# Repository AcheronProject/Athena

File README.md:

# Acheron Athena

## Introduction

Athena is a tenkeyless (TKL) keyboard Printed Circuit Board (PCB) which main feature is the multi-layout support. Athena supports:

- 87 (F12) or 88 (F13) TKL function rows;
- ANSI and ISO layouts
- 7U and 6.25U spacebar bottom row layouts
- Split backspace
- Split right shift

Below is a [Keyboard Layout Editor](http://keyboard-layout-editor.com/) image of the layouts Athena supports.

In [this link](https://raw.githubusercontent.com/Gondolindrim/file_hosting/main/athena/athena_KLE.json) there is a KLE JSON file for the layout.

Both Apollo and Athena line of PCBs were designed to be "universal" TKL PCBs, that is, designed to fit a wide variety of custom mechanical keyboards. The compatibility list is being built as more people check and test. See the **Keyboard compatibility** section of this README for the available list.

## Technical information

- Layout size: tenkeykess (TKL)
- Compatible switches: MX-like only, solderable
- Lighting: single colors per-key through-hole LEDs, RGB underglow
- Microcontroller: STM32 family (see [the Joker topologyt documentaton](https://acheronproject.com/multimcu_article/multimcu_article/))
- Connector: detachable USB Type C on the top side and JST connector for daughterboard support
- Firmware compatibility: QMK (with VIA support)
- Protection hardware:
  * USB data lines and power rail ESD suppressing
  * USB power overvoltage protection
  * Enclosure grounding pad
  * Overcurrent protection
  * LDO crowbar diode
  * EMI suppression (shielding ferrite bead)
- Current release: release Alpha-RC1 (pre-release candidate)
- Designer: Gondolindrim
- License: Acheron Open-Source Hardware License version 1.3

## Keyboard compatibility

## Known compatibilities

- **Geonworks F1-8X and F1-6X:** confirmed by Geon, who tested the PCB 3D files against the case 3D files. Live hardware testing into a machined case is pending.

### Known incompatibilities

- **ai03 KBD8X MKII**: ai03 open-sourced the PCB files for his KBD8X. Alghtough Apollo's edges do fit inside the original PCB's, its connector is more protruded then the original PCB's.

- **PrismA18**: different layouts on the function row.

## Acknowledgements

- Geon, who kindly spent time helping design this PCB to fit his keyboards.

## Copyright notice

This project is released under the Acheron Open-Hardware License V1.3. For the license, please refer to the LICENCE.md file.

The "athena with shield" logo was licensed through Adobe Stock in [this link](https://stock.adobe.com/hu/images/greek-goddess-athena-illustration/157297137); the source file in Adobe Illustrator format, with a converted ``.svg`` format  can be found in ``./resources/athena_logo``. The license was obtained in may 06, 2021 and allows the AcheronProject to redistribute the logo as open-source and allows anyone to sell the PCBs commercially, but it does not allow for reproduction, meaning that if you want to use the logo for your designs or products you will have to buy a license yourself.

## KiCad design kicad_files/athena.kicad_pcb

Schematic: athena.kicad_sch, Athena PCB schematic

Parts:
C1, C2, C7: 100n; C_0805_2012Metric
C3, C4, C5, C13: 100n; C_0402_1005Metric
C6, C14: 4.7u; C_0402_1005Metric
C8: 1u; C_0402_1005Metric
C9: 10n; C_0402_1005Metric
C10, C11: 1u; CP_EIA-3216-10_Kemet-I_Pad1.58x1.35mm_HandSolder
C12: 10u; C_0805_2012Metric
D1, D2, D3, D4, D5, D6, D7, D8, D9, D10, D11, D12, D13, D14, D15, D16, D17, D18, D19, D20, D21, D22, D23, D24, D25, D26, D27, D28, D29, D30, D31, D32, D33, D34, D35, D36, D37, D38, D39, D40, D41, D42, D43, D44, D45, D46, D47, D48, D49, D50, D51, D52, D53, D54, D55, D56, D57, D58, D59, D60, D61, D62, D63, D64, D65, D66, D67, D68, D69, D70, D71, D72, D73, D74, D75, D76, D77, D78, D79, D80, D81, D82, D83, D84, D85, D86, D87, D88, D89, D90, D91, D92, D94: 1N4148W; D_SOD-123
D93: RB060M-60TR; D_SOD-123; Manufacturer Part Number RB060M-60TR; LCSC Part Number C114257
F1: mSMD110-16V; Fuse_1812_4532Metric; Manufacturer Part Number mSMD110-16V; LCSC Part Number C69691
FB1: CBW201209U121T; L_0805_2012Metric; Manufacturer Part Number CBW201209U121T; LCSC Part Number C139186
H1: MountingHole; MountingHole_2.5x4.0mm
J1, J3: SM04B-SRSS-TB(LF)(SN); SM04B-SRSS-TB(LF)(SN)_mounting-reliefs; Manufacturer Part Number SM04B-SRSS-TB(LF)(SN); LCSC Part Number C160404
J2: TYPE-C-31-M12; TYPE-C-31-M-12; Manufacturer Part Number TYPE-C-31-M-12; LCSC Part Number C165948
J4: ARM JTAG; Conn_ARM_JTAG_SWD_6
J5: EXTRA PINS; PinHeader_1x5_P2.54mm_Vertical
Q1: DTC123JKAT146; SOT-23; Manufacturer Part Number DTC123JKAT146; LCSC Part Number C111724
R1: 10k; R_0805_2012Metric
R2, R3: 5.1k; R_0805_2012Metric
R4, R5: 1.5k; R_0402_1005Metric
R6: 100R; R_0805_2012Metric
R7, R8: 100k; R_0805_2012Metric
R9: 330k; R_0805_2012Metric
R10: 1M; R_0805_2012Metric
SW1, SW2, SW3, SW4, SW5, SW6, SW7, SW8, SW9, SW10, SW11, SW12, SW13, SW14, SW15, SW16, SW17, SW18, SW19, SW20, SW21, SW22, SW23, SW24, SW25, SW26, SW27, SW28, SW29, SW30, SW31, SW32, SW33, SW34, SW35, SW36, SW37, SW38, SW40, SW41, SW43, SW44, SW45, SW46, SW47, SW48, SW49, SW50, SW51, SW52, SW53, SW54, SW56, SW57, SW58, SW60, SW61, SW62, SW63, SW64, SW65, SW66, SW67, SW68, SW69, SW70, SW71, SW73, SW74, SW75, SW79, SW80, SW81, SW82, SW83, SW84, SW85, SW86, SW87, SW88, SW89, SW91, SW92, SW103, SW104, SW105, SW107, SW111: MX Switch; MX100
SW39: MX Switch; MX200
SW42, SW55, SW106, SW108, SW110, SW112: MX Switch; MX150
SW59, SW93: MX Switch; MX175
SW72: MX Switch; MX225R
SW76, SW94, SW95, SW96, SW97, SW99, SW100, SW101, SW102: MX Switch; MX125
SW77: MX Switch; MX_ISOEnter_Horizontal
SW78: MX Switch; MX225
SW90: MX Switch; MX275
SW98: MX Switch; MX625R
SW109: MX Switch; MX700R
SW113: K2-1187SQ-A4SW-06; Manufacturer Part Number K2-1187SQ-A4SW-06; LCSC Part Number C92584
U1: TXS0101DBVR; SOT-23-6; Manufacturer Part Number TXS0101DBVR; LCSC Part Number C132604
U2: USBLC6-2SC6; SOT-23-6; Manufacturer Part Number USBLC6-2SC6; LCSC Part Number C7519
U3: STM32F072CBT6; LQFP-48_7x7mm_P0.5mm; Manufacturer Part Number STM32F072CBT6; LCSC Part Number C81720
U4: MCP1700T-3302E/TT; SOT-23; Manufacturer Part Number MCP1700T-3302E/TT; LCSC Part Number C39051

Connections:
3V3: C1.2, C3.1, C4.1, C5.2, C6.2, C8.1, C9.1, C11.1, C13.2, C14.2, D93.2 (A), J4.1, J5.4, R1.1, R4.1, R5.1, R8.1, SW113.1 (A), U1.1 (VCCA), U3.1 (VBAT), U3.9 (VDDA), U3.24 (VDD), U3.36 (VDDIO2), U3.48 (VDD), U4.2 (VO)
5V: C2.1, C10.1, D93.1 (K), F1.2, J1.1, J3.1, R7.1, U1.6 (VCCB), U4.3 (VI)
BOOT0: C12.2, J4.6, R9.2, R10.2, U3.44 (BOOT0)
C0: SW1.2, SW26.2, SW42.2, SW59.2, SW76.1, SW78.2, SW94.2, SW95.2, SW106.2, U3.16 (PA6/ADC_IN6/TIM3_CH1/TIM16_CH1)
C1: SW2.1, SW27.1, SW43.1, SW60.1, SW79.1, SW96.1, SW107.1, U3.15 (PA5/ADC_IN5/DAC_OUT2)
C2: SW3.1, SW18.2, SW28.1, SW44.1, SW61.1, SW80.1, SW97.1, SW108.1, U3.14 (PA4/TIM14_CH1/ADC_IN4)
C3: SW4.1, SW19.2, SW29.1, SW45.1, SW62.1, SW81.1, U3.13 (PA3/TIM15_CH2/ADC_IN3)
C4: SW5.1, SW20.2, SW30.1, SW46.1, SW63.1, SW82.1, U3.12 (PA2/ADC_IN2)
C5: SW6.1, SW21.2, SW31.1, SW47.1, SW64.1, SW83.1, U3.40 (SPI1_MISO/I2S1_MCK/TIM3_CH1/PB4)
C6: SW7.1, SW32.1, SW48.1, SW65.1, SW84.1, SW98.2, SW109.2, U3.39 (SPI1_SCK/I2S1_CK/TIM2_CH2/PB3)
C7: SW8.1, SW33.1, SW49.1, SW66.1, SW85.1, U3.38 (PA15)
C8: SW9.1, SW34.1, SW50.1, SW67.1, SW86.1, U3.30 (TIM1_CH2/PA9)
C9: SW10.1, SW22.2, SW35.1, SW51.1, SW68.1, SW87.1, SW99.2, SW110.2, U3.29 (TIM1_CH1/PA8)
C10: SW11.2, SW23.1, SW36.1, SW52.1, SW69.1, SW88.1, SW100.2, U3.27 (SPI2_MISO/I2S2_MCK/I2C2_SDA/TIM15_CH1/P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)
C11: SW12.2, SW24.1, SW37.1, SW53.1, SW70.1, SW89.1, SW101.2, U3.25 (PB12)
C12: SW13.2, SW25.1, SW38.1, SW54.1, SW71.1, SW90.1, SW93.1, U3.21 (PB10/SPI2_SCK/I2C2_SCL/TIM2_CH3)
C13: SW14.1, SW39.1, SW41.1, SW55.1, SW72.1, SW77.1, SW91.1, SW102.1, SW112.1, U3.31 (TIM1_CH3/PA10)
C14: SW15.2, SW40.1, SW56.2, SW73.2, SW103.1, U3.10 (PA0/ADC_IN0)
C15: SW16.1, SW57.1, SW74.1, SW92.1, SW104.2, U3.5 (PF0/OSC_IN)
C16: SW17.1, SW58.1, SW75.1, SW105.1, U3.6 (PF1/OSC_OUT)
D+: J3.3, U2.1 (I/O1), U3.33 (USB_DP/PA12)
D-: J3.2, U2.3 (I/O2), U3.32 (USB_DM/TIM1_CH4/PA11)
DBUS+: J2.A6 (D+), J2.B6 (D+), U2.6 (I/O1)
DBUS-: J2.A7 (D-), J2.B7 (D-), U2.4 (I/O2)
GND: C1.1, C2.2, C3.2, C4.2, C5.1, C6.1, C7.2, C8.2, C9.2, C10.2, C11.2, C12.1, C13.1, C14.1, FB1.1, J1.2, J1.4, J1.MP (MountPin), J2.A1 (GND), J2.B1 (GND), J3.4, J3.MP (MountPin), J4.5, J5.5, Q1.2 (E), R2.1, R3.1, R7.2, R8.2, R10.1, U1.2 (GND), U2.2 (GND), U3.8 (VSSA), U3.23 (VSS), U3.35 (VSS), U3.47 (VSS), U4.1 (GND)
GNDPWR: FB1.2, H1.1, J2.S (SHIELD)
INTB: U3.45 (I2C1_SCL/TIM16_CH1/PB8)
NRST: C7.1, J4.3, R6.2, U3.7 (NRST)
unnamed: D1.2 (A), SW1.1
unnamed: D2.2 (A), SW2.2
unnamed: D3.2 (A), SW3.2, SW18.1
unnamed: D4.2 (A), SW4.2, SW19.1
unnamed: D5.2 (A), SW5.2, SW20.1
unnamed: D6.2 (A), SW6.2, SW21.1
unnamed: D7.2 (A), SW7.2
unnamed: D8.2 (A), SW8.2
unnamed: D9.2 (A), SW9.2
unnamed: D10.2 (A), SW10.2, SW22.1
unnamed: D11.2 (A), SW11.1, SW23.2
unnamed: D12.2 (A), SW12.1, SW24.2
unnamed: D13.2 (A), SW13.1, SW25.2
unnamed: D14.2 (A), SW14.2
unnamed: D15.2 (A), SW15.1
unnamed: D16.2 (A), SW16.2
unnamed: D17.2 (A), SW17.2
unnamed: D18.2 (A), SW26.1
unnamed: D19.2 (A), SW27.2
unnamed: D20.2 (A), SW28.2
unnamed: D21.2 (A), SW29.2
unnamed: D22.2 (A), SW30.2
unnamed: D23.2 (A), SW31.2
unnamed: D24.2 (A), SW32.2
unnamed: D25.2 (A), SW33.2
unnamed: D26.2 (A), SW34.2
unnamed: D27.2 (A), SW35.2
unnamed: D28.2 (A), SW36.2
unnamed: D29.2 (A), SW37.2
unnamed: D30.2 (A), SW38.2
unnamed: D31.2 (A), SW39.2, SW41.2
unnamed: D32.2 (A), SW40.2
unnamed: D33.2 (A), SW42.1
unnamed: D34.2 (A), SW43.2
unnamed: D35.2 (A), SW44.2
unnamed: D36.2 (A), SW45.2
unnamed: D37.2 (A), SW46.2
unnamed: D38.2 (A), SW47.2
unnamed: D39.2 (A), SW48.2
unnamed: D40.2 (A), SW49.2
unnamed: D41.2 (A), SW50.2
unnamed: D42.2 (A), SW51.2
unnamed: D43.2 (A), SW52.2
unnamed: D44.2 (A), SW53.2
unnamed: D45.2 (A), SW54.2
unnamed: D46.2 (A), SW55.2
unnamed: D47.2 (A), SW56.1
unnamed: D48.2 (A), SW57.2
unnamed: D49.2 (A), SW58.2
unnamed: D50.2 (A), SW59.1, SW76.2
unnamed: D51.2 (A), SW60.2
unnamed: D52.2 (A), SW61.2
unnamed: D53.2 (A), SW62.2
unnamed: D54.2 (A), SW63.2
unnamed: D55.2 (A), SW64.2
unnamed: D56.2 (A), SW65.2
unnamed: D57.2 (A), SW66.2
unnamed: D58.2 (A), SW67.2
unnamed: D59.2 (A), SW68.2
unnamed: D60.2 (A), SW69.2
unnamed: D61.2 (A), SW70.2
unnamed: D62.2 (A), SW71.2
unnamed: D63.2 (A), SW72.2, SW77.2
unnamed: D64.2 (A), SW73.1
unnamed: D65.2 (A), SW74.2
unnamed: D66.2 (A), SW75.2
unnamed: D67.2 (A), SW78.1, SW94.1
unnamed: D68.2 (A), SW79.2
unnamed: D69.2 (A), SW80.2
unnamed: D70.2 (A), SW81.2
unnamed: D71.2 (A), SW82.2
unnamed: D72.2 (A), SW83.2
unnamed: D73.2 (A), SW84.2
unnamed: D74.2 (A), SW85.2
unnamed: D75.2 (A), SW86.2
unnamed: D76.2 (A), SW87.2
unnamed: D77.2 (A), SW88.2
unnamed: D78.2 (A), SW89.2
unnamed: D79.2 (A), SW90.2, SW93.2
unnamed: D80.2 (A), SW91.2
unnamed: D81.2 (A), SW92.2
unnamed: D82.2 (A), SW95.1, SW106.1
unnamed: D83.2 (A), SW96.2, SW107.2
unnamed: D84.2 (A), SW97.2, SW108.2
unnamed: D85.2 (A), SW98.1, SW109.1
unnamed: D86.2 (A), SW99.1, SW110.1
unnamed: D87.2 (A), SW100.1
unnamed: D88.2 (A), SW101.1
unnamed: D89.2 (A), SW102.2, SW112.2
unnamed: D90.2 (A), SW103.2
unnamed: D91.2 (A), SW104.1
unnamed: D92.2 (A), SW105.2
unnamed: D94.1 (K), R9.1
unnamed: D94.2 (A), Q1.1 (B), SW113.2 (B)
unnamed: J2.A5 (CC1), R2.2
unnamed: J2.B5 (CC2), R3.2
unnamed: Q1.3 (C), R6.1
unnamed: R1.2, U1.5 (OE)
PC13: J5.1, U3.2 (PC13)
PC14: J5.2, U3.3 (PC14/OSC32_IN)
PC15: J5.3, U3.4 (PC15/OSC32_OUT)
R0: D1.1 (K), D2.1 (K), D3.1 (K), D4.1 (K), D5.1 (K), D6.1 (K), D7.1 (K), D8.1 (K), D9.1 (K), D10.1 (K), D11.1 (K), D12.1 (K), D13.1 (K), D14.1 (K), D15.1 (K), D16.1 (K), D17.1 (K), U3.18 (PB0/TIM3_CH3/ADC_IN8)
R1: D18.1 (K), D19.1 (K), D20.1 (K), D21.1 (K), D22.1 (K), D23.1 (K), D24.1 (K), D25.1 (K), D26.1 (K), D27.1 (K), D28.1 (K), D29.1 (K), D30.1 (K), D31.1 (K), D32.1 (K), U3.19 (PB1/TIM3_CH4/TIM14_CH1/ADC_IN9)
R2: D33.1 (K), D34.1 (K), D35.1 (K), D36.1 (K), D37.1 (K), D38.1 (K), D39.1 (K), D40.1 (K), D41.1 (K), D42.1 (K), D43.1 (K), D44.1 (K), D45.1 (K), D46.1 (K), D47.1 (K), D48.1 (K), D49.1 (K), U3.20 (PB2)
R3: D50.1 (K), D51.1 (K), D52.1 (K), D53.1 (K), D54.1 (K), D55.1 (K), D56.1 (K), D57.1 (K), D58.1 (K), D59.1 (K), D60.1 (K), D61.1 (K), D62.1 (K), D63.1 (K), D64.1 (K), D65.1 (K), D66.1 (K), U3.22 (PB11/TIM2_CH4/I2C2_SDA)
R4: D67.1 (K), D68.1 (K), D69.1 (K), D70.1 (K), D71.1 (K), D72.1 (K), D73.1 (K), D74.1 (K), D75.1 (K), D76.1 (K), D77.1 (K), D78.1 (K), D79.1 (K), D80.1 (K), D81.1 (K), U3.11 (PA1/ADC_IN1)
R5: D82.1 (K), D83.1 (K), D84.1 (K), D85.1 (K), D86.1 (K), D87.1 (K), D88.1 (K), D89.1 (K), D90.1 (K), D91.1 (K), D92.1 (K), U3.17 (PA7/TIM3_CH2/TIM14_CH1/ADC_IN7)
RGB_3V3: U1.3 (A), U3.28 (SPI2_MOSI/I2S2_SD/PB15)
RGB_5V: J1.3, U1.4 (B)
SCL: R5.2, U3.42 (I2C1_SCL/PB6)
SDA: R4.2, U3.43 (2C1_SDA/PB7)
SDB: U3.41 (SPI1_MOSI/I2S1_SD/TIM3_CH2/PB5)
SWCLK: J4.4, U3.37 (SWCLK/PA14)
SWDIO: J4.2, U3.34 (SWDIO/PA13)
VBUS: F1.1, J2.A4 (VBUS), J2.B4 (VBUS), U2.5 (VBUS)

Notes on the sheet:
USB Connector
USB ESD
MCU
SWITCH MATRIX
3V3
RGB STRIP
HARD RESET

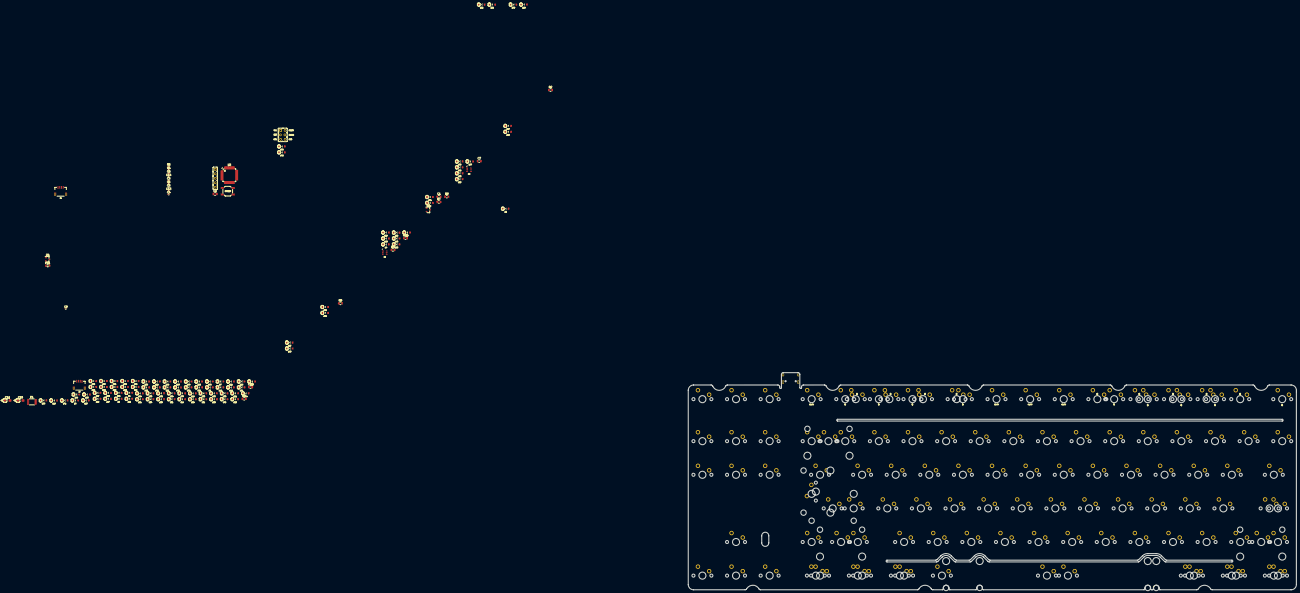
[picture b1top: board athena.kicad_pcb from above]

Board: 2 copper layers, 344.7 x 123.1 mm, 242 parts (1 on the bottom side), 140 nets, no tracks yet.

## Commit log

2021-05-07 Further developments
    - Define PCB edges
    - Place switches and layouts
    - Place USBC connector
2021-05-07 Added Athena logo
2021-05-08 Route first row and most USB, add LEDs
2021-09-25 Acheron Setup port, joker topology
    - Tolerances and constraints were updated to Acheron Setup's defaults
    - New MCU "joker" topology
2021-09-25 Update submodules
2021-09-26 Routing work
2021-09-27 Routing work, USB DB sketch
2021-09-28 More routing, DRC and post-routing pending
2021-10-01 Added logos, some DRC
2021-10-02 Add warning signs, DRC ran, errors fixed
2021-10-05 MCU circuit topology, QOL updates
    - Both RCC resistors for USB are now in the bottom layer
    - DRC ran again, no errors found
    - Changed MCU template to the joker revision 2, meaning removal of some bypass capacitors, adittion of a tantallum 10uF capacitor for VDD and change VCAP pin capacitor to 4.7uF from 2.2uF
2021-10-09 Implement B87X2 outline
2021-10-10 Documented outline, DRC
    - Outline is now B87-based and contains gummy mount holes all througout the layouts. Outline is also documented containing angles and centers.
    - DRC performed, changes and corrections made
2021-10-12 Finish documenting outlines
2021-10-12 Update component metadata
2021-12-07 Re-routes, optimizations, corrections
    - Re-routed rows R4 and R5; SWCLK pin confirmedly works as row pin as tested on pre-revision Alpha prototypes
    - Removec trace stubs on bottom left
    - Small traces optimization
2021-12-09 a-RC1 label, digital transistors
    - Label was changed to Alpha-RC1 version
    - Instead of relying on MCU open-drain pins, discrete digital NPN transistors were added to the caps lock indicator control and backlight PWM opendrain circuit
2021-12-18 Start porting to 64 pin MCU
2021-12-18 Grounding improvements
    - Grounding around MCU USB traces and connector was improved
    - For this, a couple traces were moved around, as well as a few components, most importantly the ESD chip
2021-12-18 hange LDO caps to MLCC
2021-12-18 Better grounding on top row
    - Moved traces and components for grounding pour integrity
2021-12-19 Update libs, route extra pins
2021-12-19 Add some extra pins
2021-12-19 Finish adding extra pins
2021-12-19 Adjust USB 5V routing
2021-12-19 New tag
2021-12-20 Add label to extra pins; 3V3 pour integrity adjustments
2021-12-20 New label for rev beta
2022-01-20 DRC, RGB pins
    - DRC ran, small errors corrected
    - RGB out pins from RGB DB JST connector were broken out
    - 2.0.1-2.0.1 tag
2022-01-20 Move 2nd row LED resistors for better grounding
2022-01-24 Trace improvements
2022-01-28 Start porting design to JLCPCB-compliant parts
2022-01-28 Corrections for some DRC issues
2022-01-28 More DRC corrections
2022-01-29 Add metadata to components
2022-01-29 DRC corrections, metadata add
    - Added LCSC number for missing components
    - DRC corrections: diodes courtyard overlaps
2022-01-29 Edit component metadata
2022-02-04 RGB translator change
    RGB translator changed from SC-70-6 version to SOT-563 due to JLC shortage of the former
2022-02-04 Edit component metadata; prepare for release
2022-04-05 Move top row resistors
2022-04-05 Remove RC1 from label
2022-04-05 New label
2022-04-07 DRC ran, errors corrected. Added outline cuts for H87/88 compatibility
2022-04-11 Update PCB with metadata
